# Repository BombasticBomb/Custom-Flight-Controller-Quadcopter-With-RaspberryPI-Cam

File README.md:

## Custom Drone Flight Controller
Arduino + MPU9250 based Flight Controller for Quadcopter!
This project is a custom-built quadcopter drone that uses an Arduino flight controller with an MPU9250 IMU. Will use a flight controller written in Arduino C++ with a cascaded PID loop for stabilization!
Hack Club Project (Approved): https://stardance.hackclub.com/projects/21695

## 3D Model

This'll be printed in Carbon Fiber Nylon Filament, so it is actually strong enough to be a drone chassis. I will also use a Gyroid infill pattern with 40% infill to make it really strong, and I'll also use a wall count of 6 for further reinforcement. 

## Inspiration
This is my hack club project to build a quadcopter from scratch with a custom flight controller with Arduino &amp; MPU9250. Growing up, I'd watch many science and engineering videos online; I've always been a science kid who spends his time watching astronomy, engineering, etc type videos. I did this project to challenge myself in learning the ins and outs of how a quadcopter actually works, and also to combine my skills in hardware, electronics, and coding to create something unique and not just follow a tutorial.

 ## What Makes This Project Unique
Unlike most custom drones that rely on preprogrammed ready-to-fly flight controllers, my project uses a fully custom flight controller using Arduino & mpu9250 that I had to do a lot of research to actually learn how it works using custom cascaded PID controller loops (and in the future, an extended Kalman filter), and I am working on developing it into a fully functioning firmware. Along with that, I am utilizing a novel method to stream video transmission using a USB camera and the Raspberry Pi using a Python script that uses OpenCV to play video on a web dashboard hosted in Flask and streamed with Flask-socketio. This is a unique method as I offload the low-level control to the Arduino, while I implement advanced features such as a camera (and hopefully in the future GPS, ultrasonic sensors, etc) through the more powerful Raspberry Pi, which actually runs the Linux Operating System.
- Arduino --> Does the low-level flight control and sensor fusion
- Raspberry Pi --> Video Streaming
**Note: Using the onboard wifi on the Raspberry Pi does mean the video transmission range is limited, and beyond that range, we have to rely solely on radio.

## Wiring Diagrams

| # | Arduino --> MPU9250 |   |             |
| - | ----------------- | - | ----------- |
|   | **Arduino**       | --> | **MPU9250** |
|   | 5V                | --> | 5V          |
|   | GND               | --> | GND         |
|   | A4                | --> | SDA         |
|   | A5                | --> | SCL         |

| # | Arduino --> RC Receiver |   |                 |
| - | --------------------- | - | --------------- |
|   | **Arduino**           | --> | **RC Receiver** |
|   | 5V                    | --> | 5V              |
|   | GND                   | --> | GND             |
|   | RX                    | --> | IBus            |

| # | Arduino --> ESC |   |         |
| - | ------------- | - | ------- |
|   | **Arduino**   | --> | **ESC** |
|   | 5V            | --> | 5V      |
|   | GND           | --> | GND     |
|   | 3             | --> | ESC1    |
|   | 4             | --> | ESC2    |
|   | 5             | --> | ESC3    |
|   | 6             | --> | ESC4    |

## Custom PCB:

Note: The ESCs themselves are part of the wiring diagram and are powered by the Arduino. It is crucial to note the motors themselves, and the Arduino also gets power from the main battery. The reason this configuration was required is that the Arduino converts the 11.1V on the 3S battery to 5V and supplies it to the other electronics.

# Bill of Materials

| Name | Purpose | Quantity | Total Cost (USD) | Link | Distributor |
|------|---------|----------|------------------|------|-------------|
| EVE 50PL 21700 5000mAh 50A Battery | This'll power the drone through its flight. I decided to buy Li-ion batteries and manually connect 3 to make a 3S cell to make a 5000mAh 3S battery pack. This'll help the drone fly longer. I'm buying one extra just in case. | 4 | 24.00 | https://www.18650batterystore.com/products/eve-50pl-21700-5000mah-50a-battery?variant=46405896798359 | 18650 Battery Store |
| JLCPCB Order + Shipping | I'll be manufacturing my custom PCB from JLCPCB. | 1 | 4.30 | https://cart.jlcpcb.com/quote?stencilLayer=2&stencilWidth=100&stencilLength=100&stencilCounts=5&plateType=1&spm=Jlcpcb.Homepage.1010 | JLCPCB |
| Male & Female Headers | It'll be used to connect things on the PCB. | 1 | 3.82 | https://www.aliexpress.us/item/3256805860047704.html?spm=a2g0o.cart.0.0.347038daeMTzKz&mp=1&pdp_npi=6%40dis%21USD%21USD%202.56%21USD%202.48%21%21USD%202.48%21%21%21%40210311a017759634443543759ee48c%2112000035473388533%21ct%21US%212842570567%21%211%210%21&_gl=1*hb3qht*_gcl_aw*R0NMLjE3NzU5NjE3NjQuQ2p3S0NBanc0dWZPQmhCa0Vpd0FmdUM3LVN4Wk1VVThydWVYUFUtRldvTkVNRkdlU1g5UkxIbzBkY1JpdmRNRlpicjZjYzA5cVpvUTNCb0Nxb3dRQXZEX0J3RQ..*_gcl_au*MTA5ODg3MDg0OS4xNzc0MTUwMTU1*_ga*MTgzMDIyMjAwNi4xNzc1OTYyMjM1*_ga_VED1YSGNC7*czE3NzU5NjIyMzQkbzEkZzEkdDE3NzU5NjM0NTAkajIzJGwwJGgw&gatewayAdapt=glo2usa | AliExpress |
| XT90 Male to XT60 Female connector for battery | This converts the XT90 on the battery to XT60 so it can be connected to the PCB. | 1 | 1.00 | https://www.aliexpress.us/item/3256809870073827.html?spm=a2g0o.productlist.main.2.6ec677250MQCzi&algo_pvid=cdafdfe4-f998-4543-be9e-b0735b928c6e&algo_exp_id=cdafdfe4-f998-4543-be9e-b0735b928c6e-1&pdp_ext_f=%7B%22order%22%3A%22124%22%2C%22spu_best_type%22%3A%22price%22%2C%22eval%22%3A%221%22%2C%22fromPage%22%3A%22search%22%7D&pdp_npi=6%40dis%21USD%2111.54%210.99%21%21%2179.06%216.79%21%402103212317741506875214915ecc89%2112000050973827105%21sea%21US%210%21ABX%211%210%21n_tag%3A-29910%3Bd%3Af626b5c8%3Bm03_new_user%3A-29895%3BpisId%3A5000000197847475&curPageLogUid=TNcZo29qJmvN&utparam-url=scene%3Asearch%7Cquery_from%3A%7Cx_object_id%3A1005010056388579%7C_p_origin_prod%3A | AliExpress |
| Drone Frame | This will be the frame that I will be doing all the testing on. I'll have to ship it to my location. | 1 | 5.00 | https://github.com/hackclub/print-legion | Hack Club Legion |
| 1400KV Brushless Motors | These will be the motors that generate lift for the drone. | 4 | 33.40 | https://www.robotshop.com/products/e-s-motor-xxd-a2212-brushless-motor-160w-mounting-base-kits-kv-1400?qd=f82c3b340c3f619c5c40ab447d536a69 | Robotshop |
| Raspberry PI 4 4GB | This will be used to connect the USB camera and for video transmission. I already have this, so I will not need to buy it. | 1 | 0.00 | https://www.centralcomputer.com/raspberry-pi-4-model-b-rpi4-modbp-4gb-4gb-ddr4-ram-bcm2711-soc-usb-3-0-poe-enabled.html | Central Computers |
| Arduino Nano | This will be running the flight software and controlling the motors. I already have this, so I will not need to buy it. | 1 | 0.00 | https://www.aliexpress.us/item/3256809956121978.html?aem_p4p_detail=2026061807213415670671290773640000102442&algo_pvid=3fc0e9e0-2e6c-470b-8047-724649fb7564&algo_exp_id=3fc0e9e0-2e6c-470b-8047-724649fb7564-3&pdp_ext_f=%7B%22order%22%3A%222454%22%2C%22eval%22%3A%221%22%2C%22fromPage%22%3A%22search%22%7D&pdp_npi=6%40dis%21USD%213.74%212.32%21%21%2125.14%2115.59%21%402103128817817924947762687ecb01%2112000051298773766%21sea%21US%210%21ABX%211%210%21n_tag%3A-29910%3Bd%3A3fe947d3%3Bm03_new_user%3A-29895&curPageLogUid=GvMORCvxgsTu&utparam-url=scene%3Asearch%7Cquery_from%3A%7Cx_object_id%3A1005010142436730%7C_p_origin_prod%3A&search_p4p_id=2026061807213415670671290773640000102442_1 | AliExpress |
| GY-91 Board with both MPU-9250 & BMP180 | This will the the 9 Axis Flight Controller for the drone (Gyroscope, Accelerometer, Magnetometer, Altometer). | 1 | 6.34 | https://www.aliexpress.us/item/3256810419378175.html?spm=a2g0o.productlist.main.5.666b2322l9xEzg&algo_pvid=7fd4cfff-d2cf-4cf7-afad-2ea0b819e83e&algo_exp_id=7fd4cfff-d2cf-4cf7-afad-2ea0b819e83e-4&pdp_ext_f=%7B%22order%22%3A%2249%22%2C%22eval%22%3A%221%22%2C%22fromPage%22%3A%22search%22%7D&pdp_npi=6%40dis%21USD%217.21%216.34%21%21%217.21%216.34%21%402101ef5e17817925960768424e7f71%2112000058167636174%21sea%21US%210%21ABX%211%210%21n_tag%3A-29910%3Bd%3A3fe947d3%3Bm03_new_user%3A-29895&curPageLogUid=rwzrzHfS3o8g&utparam-url=scene%3Asearch%7Cquery_from%3A%7Cx_object_id%3A1005010605692927%7C_p_origin_prod%3A | AliExpress |
| 8x4.5 Inch RC Drone Propellers | These will be used on the brushless motors to provide lift for the drone. I am buying 8 pieces instead of 4 in case some break during testing. | 1 | 0.92 | https://www.aliexpress.us/item/2251832730802090.html?spm=a2g0o.productlist.main.4.780ePWPrPWPrdV&algo_pvid=f486226a-b9b0-4b15-9514-1ad157b2ce74&algo_exp_id=f486226a-b9b0-4b15-9514-1ad157b2ce74-3&pdp_ext_f=%7B%22order%22%3A%22290%22%2C%22eval%22%3A%221%22%2C%22fromPage%22%3A%22search%22%7D&pdp_npi=6%40dis%21USD%211.14%210.92%21%21%211.14%210.92%21%402103126e17817925437511508e4a1e%2165941027930%21sea%21US%210%21ABX%211%210%21n_tag%3A-29910%3Bd%3A3fe947d3%3Bm03_new_user%3A-29895&curPageLogUid=cXlmlSlAPHTO&utparam-url=scene%3Asearch%7Cquery_from%3A%7Cx_object_id%3A32917116842%7C_p_origin_prod%3A | AliExpress |
| 3S Li-po Battery Charger US Plug | This will be used to charge the battery. | 1 | 11.61 | https://www.aliexpress.us/item/3256805934795867.html?spm=a2g0o.productlist.main.5.5574546cUwMiyN&algo_pvid=89444658-625e-497a-9161-8886d6b7c66c&algo_exp_id=89444658-625e-497a-9161-8886d6b7c66c-4&pdp_ext_f=%7B%22order%22%3A%2236%22%2C%22eval%22%3A%221%22%2C%22fromPage%22%3A%22search%22%7D&pdp_npi=6%40dis%21USD%2114.61%219.61%21%21%2114.61%219.61%21%402103122117759642911075864e8f33%2112000035846729871%21sea%21US%212842570567%21ACX%211%210%21n_tag%3A-29919%3Bd%3A3fe947d3%3Bm03_new_user%3A-29894%3BpisId%3A5000000203531302&curPageLogUid=vJ4Xx6RcBVto&utparam-url=scene%3Asearch%7Cquery_from%3A%7Cx_object_id%3A1005006121110619%7C_p_origin_prod%3A | AliExpress |
| MicroZone MC6C Mini V2 2.4G 6CH Controller Transmitter w/ Receiver | This will be used for the radio communication with the drone. | 1 | 35.24 | https://www.aliexpress.us/item/3256807243819244.html?spm=a2g0o.productlist.main.35.4ab577e7dXjt8P&algo_pvid=51c9d117-d897-430c-8a26-849a75ee0eb6&algo_exp_id=51c9d117-d897-430c-8a26-849a75ee0eb6-34&pdp_ext_f=%7B%22order%22%3A%22543%22%2C%22eval%22%3A%221%22%2C%22fromPage%22%3A%22search%22%7D&pdp_npi=6%40dis%21USD%21118.36%2135.24%21%21%21804.10%21239.42%21%40210319b717759622763998627ecd25%2112000040726294727%21sea%21US%212842570567%21ACX%211%210%21n_tag%3A-29919%3Bd%3A3fe947d3%3Bm03_new_user%3A-29894%3BpisId%3A5000000203531302&curPageLogUid=uuj3pbufhNDE&utparam-url=scene%3Asearch%7Cquery_from%3A%7Cx_object_id%3A1005007430133996%7C_p_origin_prod%3A | AliExpress |
| 30A Brushless Motor ESC | This will be the Electronic Speed Controller for the 4 brushless motors on the drone. I need to buy 2 pieces for a total of 4 for each motor. | 1 | 12.87 | https://www.aliexpress.us/item/2252799818726193.html?spm=a2g0o.detail.0.0.57c84iEw4iEwcX&mp=1&pdp_npi=6%40dis%21USD%21USD%2019.37%21USD%2012.87%21%21USD%2012.87%21%21%21%402101e62517759623597128640e4864%2112000037347798186%21ct%21US%212842570567%21%211%210%21&_gl=1*bd7qv0*_gcl_aw*R0NMLjE3NzU5NjE3NjQuQ2p3S0NBanc0dWZPQmhCa0Vpd0FmdUM3LVY5UkxIbzBkY1JpdmRNRlpicjZjYzA5cVpvUTNCb0Nxb3dRQXZEX0J3RQ..*_gcl_au*MTA5ODg3MDg0OS4xNzc0MTUwMTU1*_ga*MTgzMDIyMjAwNi4xNzc1OTYyMjM1*_ga_VED1YSGNC7*czE3NzU5NjIyMzQkbzEkZzEkdDE3NzU5NjIzNjEkajEwJGwwJGgw&gatewayAdapt=glo2usa | AliExpress |
| 12V-5V Buck Converter | This'll convert the 11.1V from the 21700 battery pack to 5V so the Raspberry PI can use it. | 1 | 0.99 | https://www.aliexpress.us/item/3256806059787124.html?spm=a2g0o.productlist.main.47.356d56843bI7xm&algo_pvid=37468c4f-56f3-46fc-b45b-78fc5e97108e&algo_exp_id=37468c4f-56f3-46fc-b45b-78fc5e97108e-44&pdp_ext_f=%7B%22order%22%3A%228%22%2C%22eval%22%3A%221%22%2C%22fromPage%22%3A%22search%22%7D&pdp_npi=6%40dis%21USD%211.57%210.99%21%21%211.57%210.99%21%402101e2b217831438404382735e9fc9%2112000036452024405%21sea%21US%210%21ABX%211%210%21n_tag%3A-29910%3Bd%3A3fe947d3%3Bm03_new_user%3A-29895%3BpisId%3A5000000207260799&curPageLogUid=bAlAl3PlYxYP&utparam-url=scene%3Asearch%7Cquery_from%3A%7Cx_object_id%3A1005006246101876%7C_p_origin_prod%3A | AliExpress |
| **Total** | | | **139.49** | | |

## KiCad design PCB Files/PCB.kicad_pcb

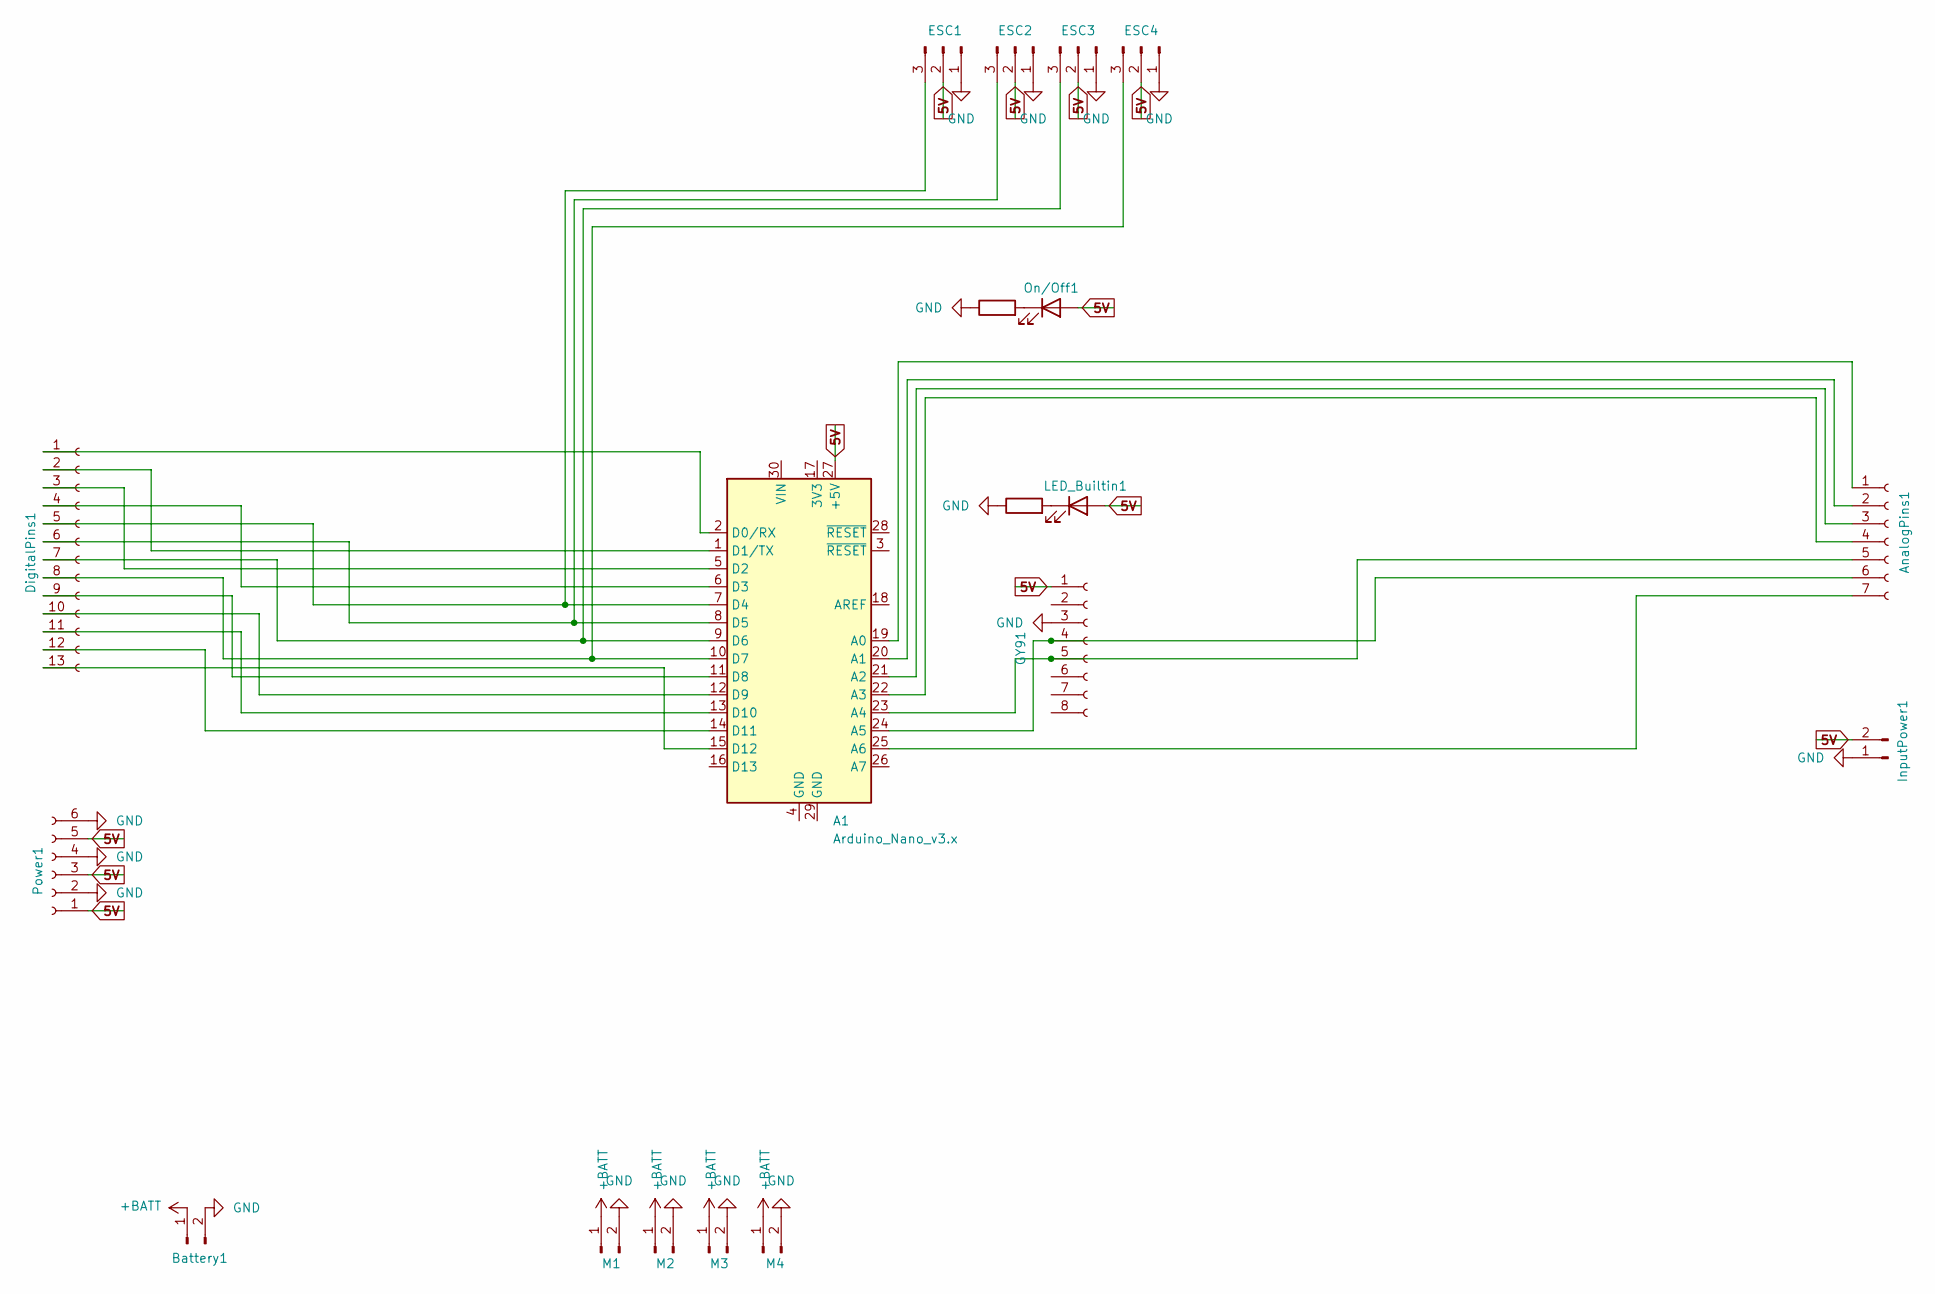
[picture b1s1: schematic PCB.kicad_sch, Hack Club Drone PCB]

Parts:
A1: Arduino_Nano_v3.x; Arduino_Nano
AnalogPins1: Conn_01x07_Socket; PinSocket_1x07_P2.54mm_Vertical
Battery1: Conn_01x02_Pin; AMASS_XT60PW-M_1x02_P7.20mm_Horizontal
DigitalPins1: Conn_01x13_Socket; PinSocket_1x13_P2.54mm_Vertical
ESC1, ESC2, ESC3, ESC4: Conn_01x03_Pin; PinSocket_1x03_P2.54mm_Vertical
GY91: Conn_01x08_Socket; PinSocket_1x08_P2.54mm_Vertical
InputPower1: Conn_01x02_Pin; PinSocket_1x02_P2.54mm_Vertical
LED_Builtin1: LED; LED_D5.0mm
M1, M2, M3, M4: Conn_01x02_Pin; AMASS_XT60PW-M_1x02_P7.20mm_Horizontal
On/Off1: ON/OFF; LED_D5.0mm
Power1: Conn_01x06_Socket; PinSocket_1x06_P2.54mm_Vertical
R220-1, R220-2: 220; R_Axial_DIN0207_L6.3mm_D2.5mm_P10.16mm_Horizontal

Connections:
5V: A1.27 (+5V), ESC1.2, ESC2.2, ESC3.2, ESC4.2, GY91.1, InputPower1.2, LED_Builtin1.2 (A), On/Off1.2 (A), Power1.1, Power1.3, Power1.5
+BATT: Battery1.1, M1.1, M2.1, M3.1, M4.1
GND: Battery1.2, ESC1.1, ESC2.1, ESC3.1, ESC4.1, GY91.3, InputPower1.1, M1.2, M2.2, M3.2, M4.2, Power1.2, Power1.4, Power1.6, R220-1.1, R220-2.1
unnamed: A1.19 (A0), AnalogPins1.1
unnamed: A1.20 (A1), AnalogPins1.2
unnamed: A1.21 (A2), AnalogPins1.3
unnamed: A1.22 (A3), AnalogPins1.4
unnamed: A1.23 (A4), AnalogPins1.5, GY91.5
unnamed: A1.24 (A5), AnalogPins1.6, GY91.4
unnamed: A1.25 (A6), AnalogPins1.7
unnamed: A1.2 (D0/RX), DigitalPins1.1
unnamed: A1.1 (D1/TX), DigitalPins1.2
unnamed: A1.5 (D2), DigitalPins1.3
unnamed: A1.6 (D3), DigitalPins1.4
unnamed: A1.7 (D4), DigitalPins1.5, ESC1.3
unnamed: A1.8 (D5), DigitalPins1.6, ESC2.3
unnamed: A1.9 (D6), DigitalPins1.7, ESC3.3
unnamed: A1.10 (D7), DigitalPins1.8, ESC4.3
unnamed: A1.11 (D8), DigitalPins1.9
unnamed: A1.12 (D9), DigitalPins1.10
unnamed: A1.13 (D10), DigitalPins1.11
unnamed: A1.14 (D11), DigitalPins1.12
unnamed: A1.15 (D12), DigitalPins1.13
unnamed: LED_Builtin1.1 (K), R220-2.2
unnamed: On/Off1.1 (K), R220-1.2

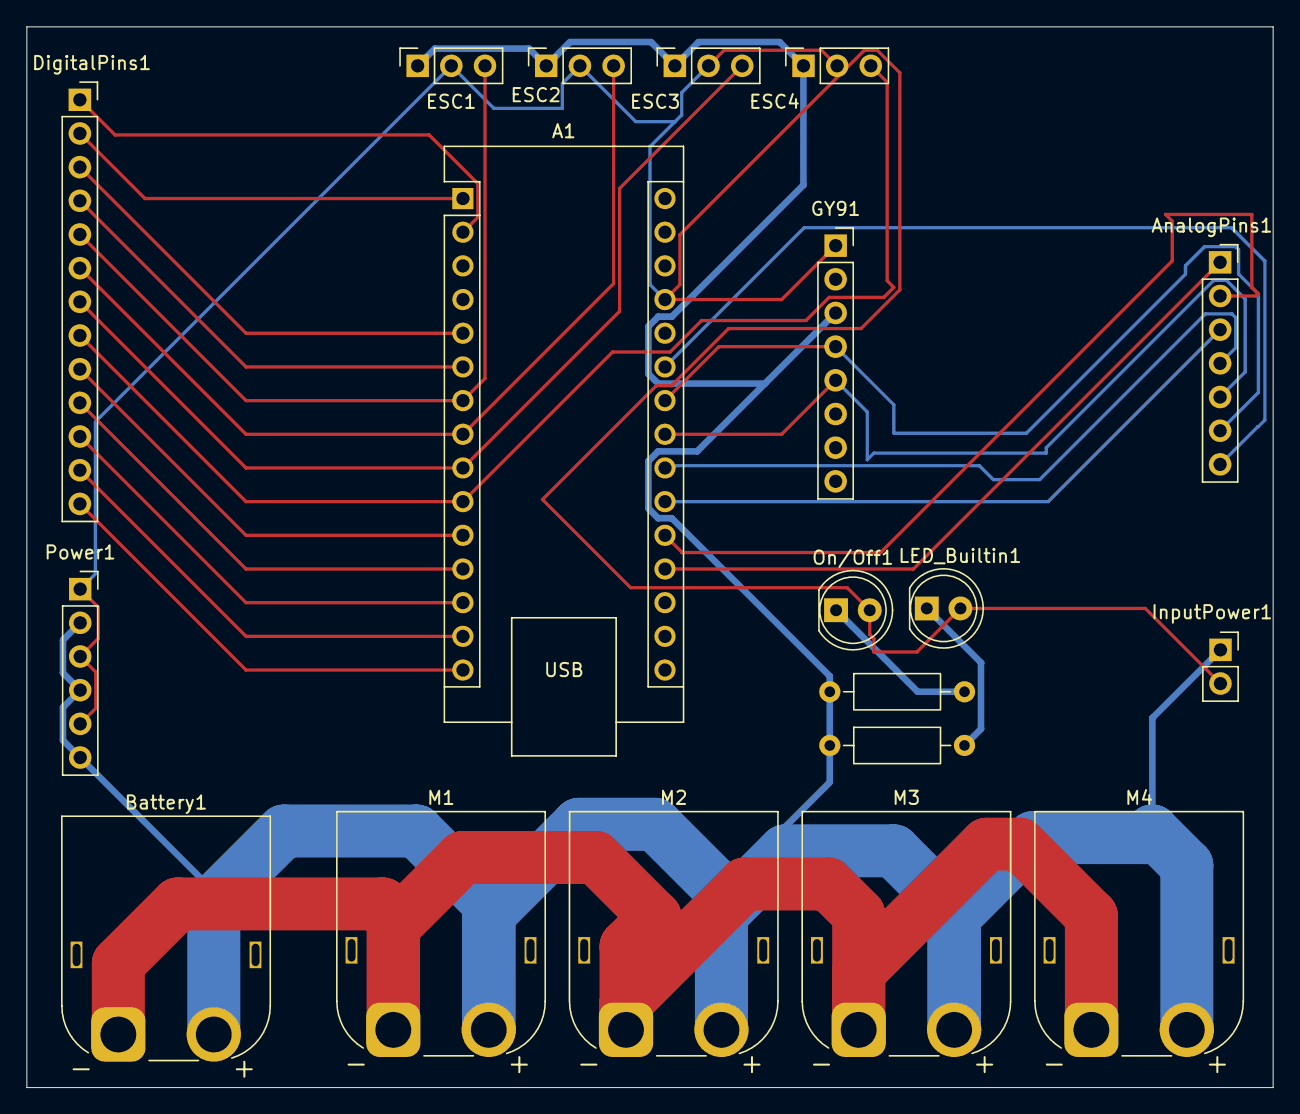
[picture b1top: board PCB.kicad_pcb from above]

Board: 2 copper layers, 94.0 x 80.0 mm, 19 parts (0 on the bottom side), 25 nets.

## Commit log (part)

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2026-03-18 Replace old image with new model image
    Updated the image in the README to a new model image.
2026-03-18 Update README with 3D model details
    Added information about the 3D model and its location in the releases section.
2026-03-18 Clarify drone's camera usage in README
    Updated description for clarity on drone's functionality.
2026-03-19 Update MPU6050 to MPU9250 in project description
2026-03-23 Update drone frame cost and total cost
    Updated the cost of the drone frame from $15.00 to $22.00, resulting in a new total cost of $198.79 USD.
2026-03-23 File management
2026-03-23 rename
2026-03-23 Refine README content and remove unnecessary notes
    Removed redundant notes and improved clarity in the Bill of Materials section.
2026-03-23 Replace 3D model image in README
    Updated the 3D model image in the README.
2026-04-12 PCB Layout
2026-04-18 Added PCB Files
2026-05-09 Add unzipping instructions for Final_Drone.step
    Add instructions for unzipping the Final_Drone.step file.
2026-05-09 Update README with additional 3D model image
    Added a new image to the 3D Model section of the README.
2026-05-09 Enhance README with project inspiration and uniqueness
    Added details about the project's uniqueness and inspiration for building a custom flight controller.
2026-06-03 Revise project inspiration section in README
    Removed personal reflections and streamlined project description.
2026-06-03 updated pcb files
2026-06-10 Revise README with new project details and image
    Updated project description and added new image.
2026-06-10 Added new 3D files
2026-06-11 Update images and project description in README
    Updated images in the README to reflect new assets and improved descriptions of the project.
2026-06-11 changed designs for chassis
2026-06-11 added the proper files
    Last time I accidentally uploaded outdated files, these are the latest ones.
2026-06-12 Added another hole to the arm for stability
2026-06-12 CAD Arms Design Changes
    Made more changes to the drone arms including their thickness to make them much more sturdier to shocks and crashes. This should prove vital during testing.
2026-06-12 Adjust total cost in README
    Updated the total cost of the components listed in the README.
2026-06-13 Added curved shapes for improved aerodynamics
2026-06-13 Replace 3D model image URL in README
    Updated the 3D model image in the README with a new link.
2026-06-13 Added Brushless Motors
2026-06-13 Renamed bom.csv
2026-06-14 Flipped Screw hole positions
2026-06-15 Replaced back
2026-06-15 Fixed motor wheels and added bumps for shock absorbers later
2026-06-18 Revise README with new project details and image
    Updated project description and replaced an image link.
2026-06-18 Added Landing Legs
    Added proper landing legs with screw holes to attach it to the main body.
2026-06-19 Revise Bill of Materials in README.md
    Updated the Bill of Materials section with additional components and corrected some entries.
2026-06-19 Update BOM.csv
    Updated BOM.csv with new parts and replaced or corrected old parts.
2026-06-19 Added the demo video
2026-06-19 Create Past_JOURNAL.md
    Added the past journal from Stasis that tracked my work from the beginning so that reviewers can verify my work.
2026-06-19 Replace 3D model image URL in README
    Updated the 3D model image in the README to a new source.
2026-06-19 Added an area for the electronics
2026-06-19 Replace drone image with new 3D model
    Updated the 3D model image in the README.
2026-06-20 Made landing legs shorter to make drone more stable and resistant to toppling over
2026-06-20 Fixed holes from m2 to m3, i accidentally switched them
2026-06-26 Create MPU9250_IMU.ino
    Added a new IMU file for the updated MPU9250 instead of the old MPU6050
